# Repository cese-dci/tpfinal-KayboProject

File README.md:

# TP Diseño de Circuitos Impresos [CESE 10Co2019 DCI]
## Autor: Yapura Alberto Emanuel
## Alumno revisor: Del Sancio Leonardo Daniel
### Descripción:

El Acelerómetro consiste en una placa de conexión para el chip ADXL345 de Analog Devices Inc., un acelerómetro de triple eje con interfaces I2C y SPI. Gracias a un regulador y un convertidor de nivel lógico, puede interactuar con microcontroladores de 3V y 5V.

El sensor toma medidas en tres ejes, XY y Z, y puede comunicarse a través de interfaces digitales. I2C y SPI. Puede establecer el nivel de sensibilidad en + -2g, + - 4g, + - 8g o + -16g. El rango más bajo permite una resolución más alta para movimientos lentos, el rango más alto es mejor para rastrear altas velocidades. El chip ADXL345 es uno de los mejores sensores de Analog Devices, conocido por su calidad excepcional como dispositivo MEMS (sistema microelectromecánico). El pin VIN toma hasta 5V de entrada y lo ajusta a 3,3V, disponible

**Características:**
- Sensor Analog Devices ADXL 345
- Alimentación: 3.3 a 5V
- Comunicación: I2C o SPI
- Sensibilidad configurable: +-2g/4g/8g/16g
- Dimensiones: 25x22 mm
- Peso: 1.27 gramos

El proyecto consiste en el diseño utilizando la herramienta Kicat de una **Replica del Acelerómetro adxl345**.

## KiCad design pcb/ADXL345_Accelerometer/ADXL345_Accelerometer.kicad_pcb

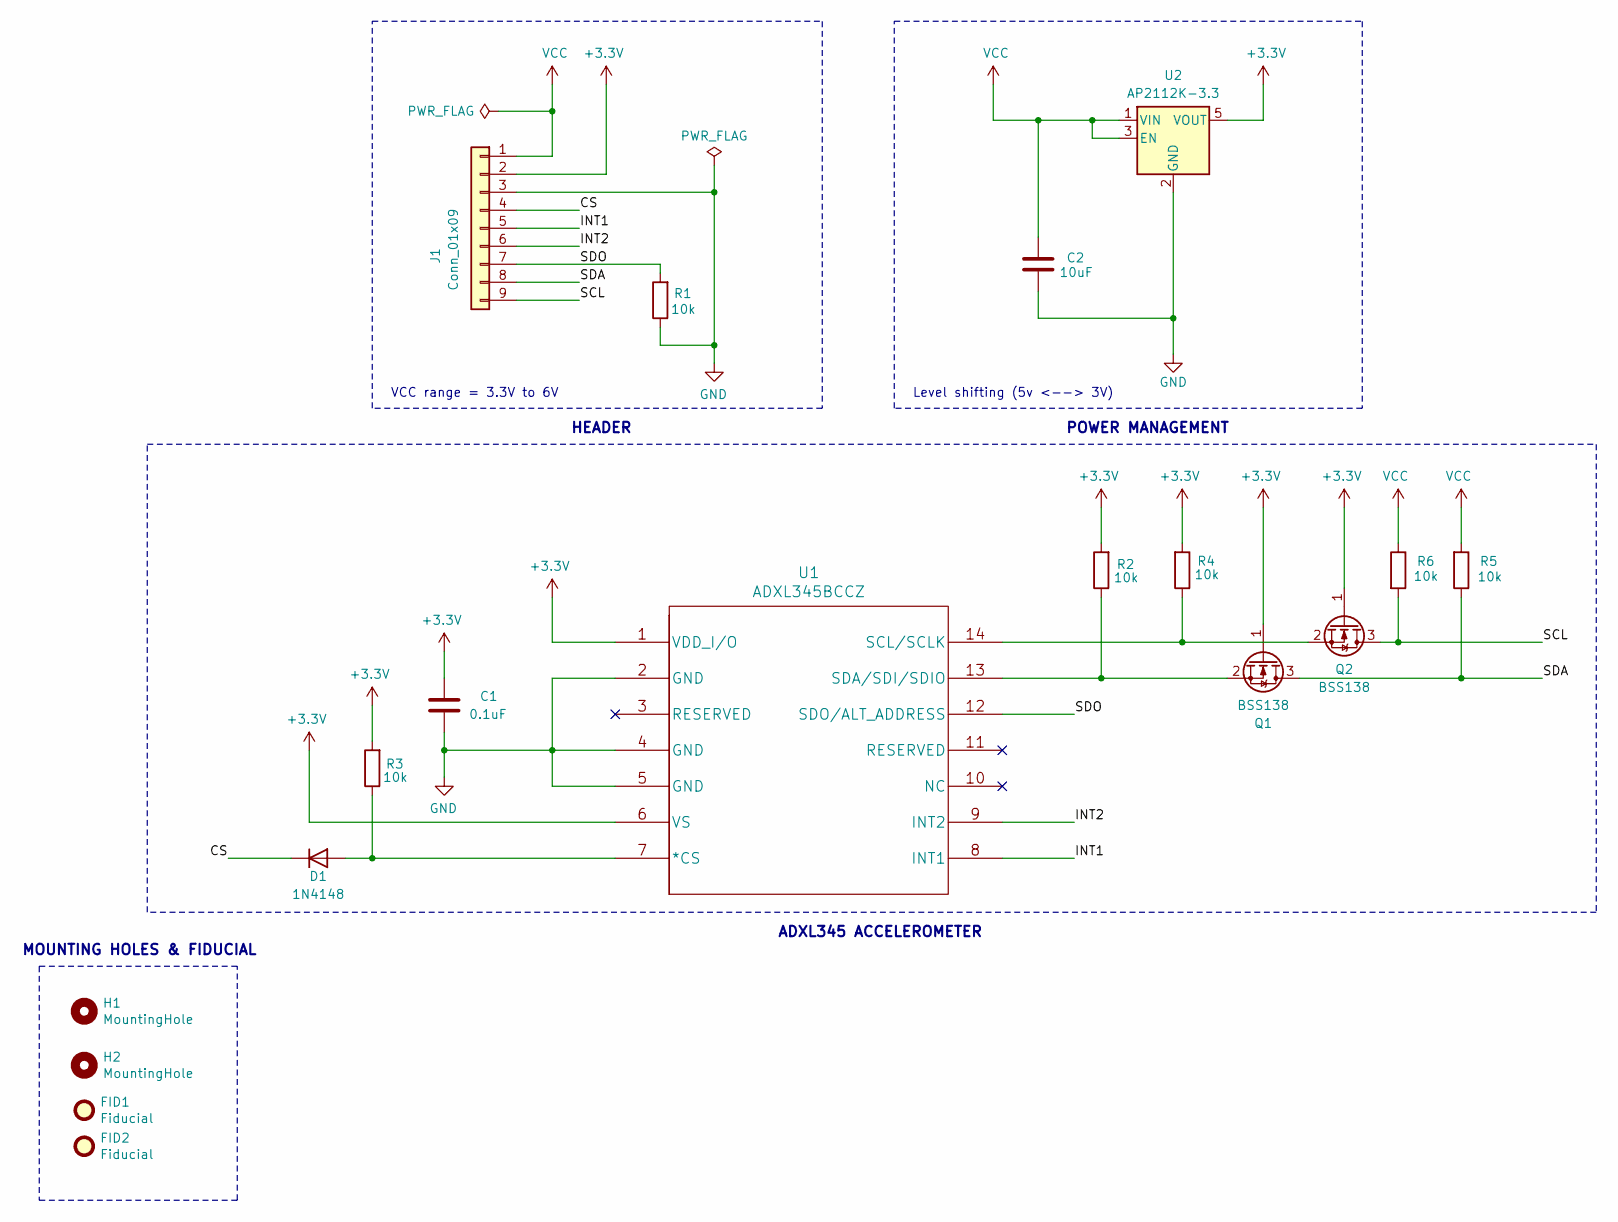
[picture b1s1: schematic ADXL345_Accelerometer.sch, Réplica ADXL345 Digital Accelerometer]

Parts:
C1: 0.1uF; C_0805_2012Metric
C2: 10uF; C_0805_2012Metric
D1: 1N4148; D_0805_2012Metric
FID1, FID2: Fiducial; Fiducial_0.5mm_Mask1.5mm
H1, H2: MountingHole; MountingHole_2.5mm_Pad
J1: Conn_01x09; PinHeader_1x09_P2.54mm_Vertical; Digi-Key 10129378-909003BLF-ND
Q1, Q2: BSS138; SOT-23; Digi-Key BSS138CT-ND
R1, R2, R3, R4, R5, R6: 10k; D_0805_2012Metric
U1: ADXL345BCCZ; LGA-14_3x5mm_P0.8mm_LayoutBorder1x6y; Digi-Key ADXL345BCCZ-ND
U2: AP2112K-3.3; SOT-23-5; Digi-Key AP2112K-3.3TRG1DITR-ND

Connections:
+3V3: C1.2, J1.2, Q1.1 (G), Q2.1 (G), R2.2, R3.2, R4.2, U1.1 (VDD_I/O), U1.6 (VS), U2.5 (VOUT)
/CS: D1.1 (K), J1.4
/INT1: J1.5, U1.8 (INT1)
/INT2: J1.6, U1.9 (INT2)
/SCL: J1.9, Q2.3 (D), R6.2
/SDA: J1.8, Q1.3 (D), R5.1
/SDO: J1.7, R1.2, U1.12 (SDO/ALT_ADDRESS)
GND: C1.1, C2.2, J1.3, R1.1, U1.2 (GND), U1.4 (GND), U1.5 (GND), U2.2 (GND)
unnamed: D1.2 (A), R3.1, U1.7 (*CS)
unnamed: Q1.2 (S), R2.1, U1.13 (SDA/SDI/SDIO)
unnamed: Q2.2 (S), R4.1, U1.14 (SCL/SCLK)
VCC: C2.1, J1.1, R5.2, R6.1, U2.1 (VIN), U2.3 (EN)

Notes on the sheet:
MOUNTING HOLES & FIDUCIAL
ADXL345 ACCELEROMETER
Level shifting (5v <--> 3V)
VCC range = 3.3V to 6V
POWER MANAGEMENT
HEADER

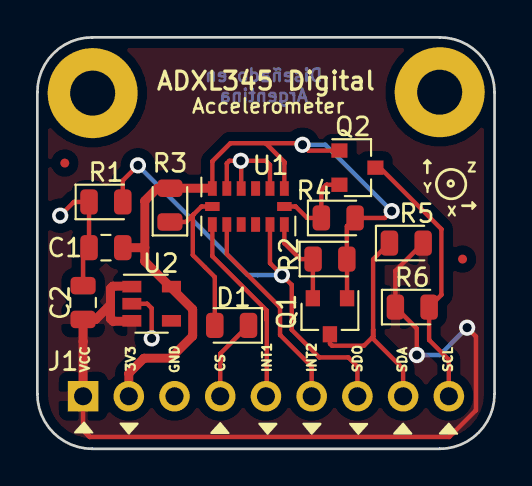
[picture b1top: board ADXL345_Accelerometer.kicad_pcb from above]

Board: 2 copper layers, 25.4 x 22.9 mm, 18 parts (1 on the bottom side), 12 nets.

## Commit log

2020-06-08 Primer commit
    Para corregir.
2020-06-09 Correcciones
    Se corrigieron de acuerdo a las recomendaciones realizadas por el alumno revisor.
2020-06-18 Correcciones
    Se corrigieron segun las recomendaciones realizadas por el docente.
2020-06-19 Correcciones
    Se corrigieron detalles y se agregaron códigos de catálogo recomendados.
2020-06-27 Se agregaron fiduciales
2020-07-02 Correcciones
    Se hicieron las correcciones de acuerdo a las recomendaciones del docente.
2020-07-02 Modelos 3D del proyecto
2020-07-03 Modelos 3D
    Se generaron los modelos 3D.
2020-07-10 Correcciones
    Se corrigio de acuerdo a las ultimas recomendaciones realizadas por el docente.
2020-07-13 Correccciones

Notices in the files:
pcb/ADXL345_Accelerometer/ADXL345_Accelerometer.kicad_pcb:
Bajo Licencia Creative Commons Attribution Sharealike 4.0
pcb/ADXL345_Accelerometer/ADXL345_Accelerometer.sch:
https://creativecommons.org/licenses/by-sa/4.0
